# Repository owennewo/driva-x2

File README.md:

# driva-x2
Experimental dual BLDC board for use with [SimpleFOC](https://simplefoc.com)

This board will cost about $200 for 5 units from JLCPCB. Include are [gerber zip](https://github.com/owennewo/driva-x2/blob/main/kicad/gerber/driva-x2.zip), [BOM](https://github.com/owennewo/driva-x2/blob/main/kicad/assembly/driva-x2-bom.csv) and [POS](https://github.com/owennewo/driva-x2/blob/main/kicad/assembly/driva-x2-all-pos.csv).  Designed in Kicad.  This is pre-alpha quality e.g. I'm uncertain how much of it will work.  I've tested v0.5 with motor and hall sensors on left motor and that worked.

 - dual motor drivers using 3x btn8982 or ixf0007s
 - each motor has hall and spi port (untested)
 - prog (swd, swdio), can (untested), usart and i2c (untested) ports
 - ubg-otg (utested and without 5v attached)
 - onboard mpu6050 for 6 axis imu

Note JLCPCB won't do through hole components therefore all power, motor, comms ports will need to be hand solder as will the 1000uF cap.  

The BOM and Pick/Place/POS file are here:
https://github.com/owennewo/driva-x2/tree/main/kicad/assembly 

[PDF Schematic](./kicad/docs/driva-x2.pdf)

The gerber files are here:
https://github.com/owennewo/driva-x2/tree/main/kicad/gerber

The BOM and Pick/Place/POS file are here:
https://github.com/owennewo/driva-x2/tree/main/kicad/assembly

 * v0.5 - First attempt (partly working - problems with mpu6050, can and LDO)
 * v0.9 - Second attempt (fixed above hopefully - awaiting order from JLCPCB)

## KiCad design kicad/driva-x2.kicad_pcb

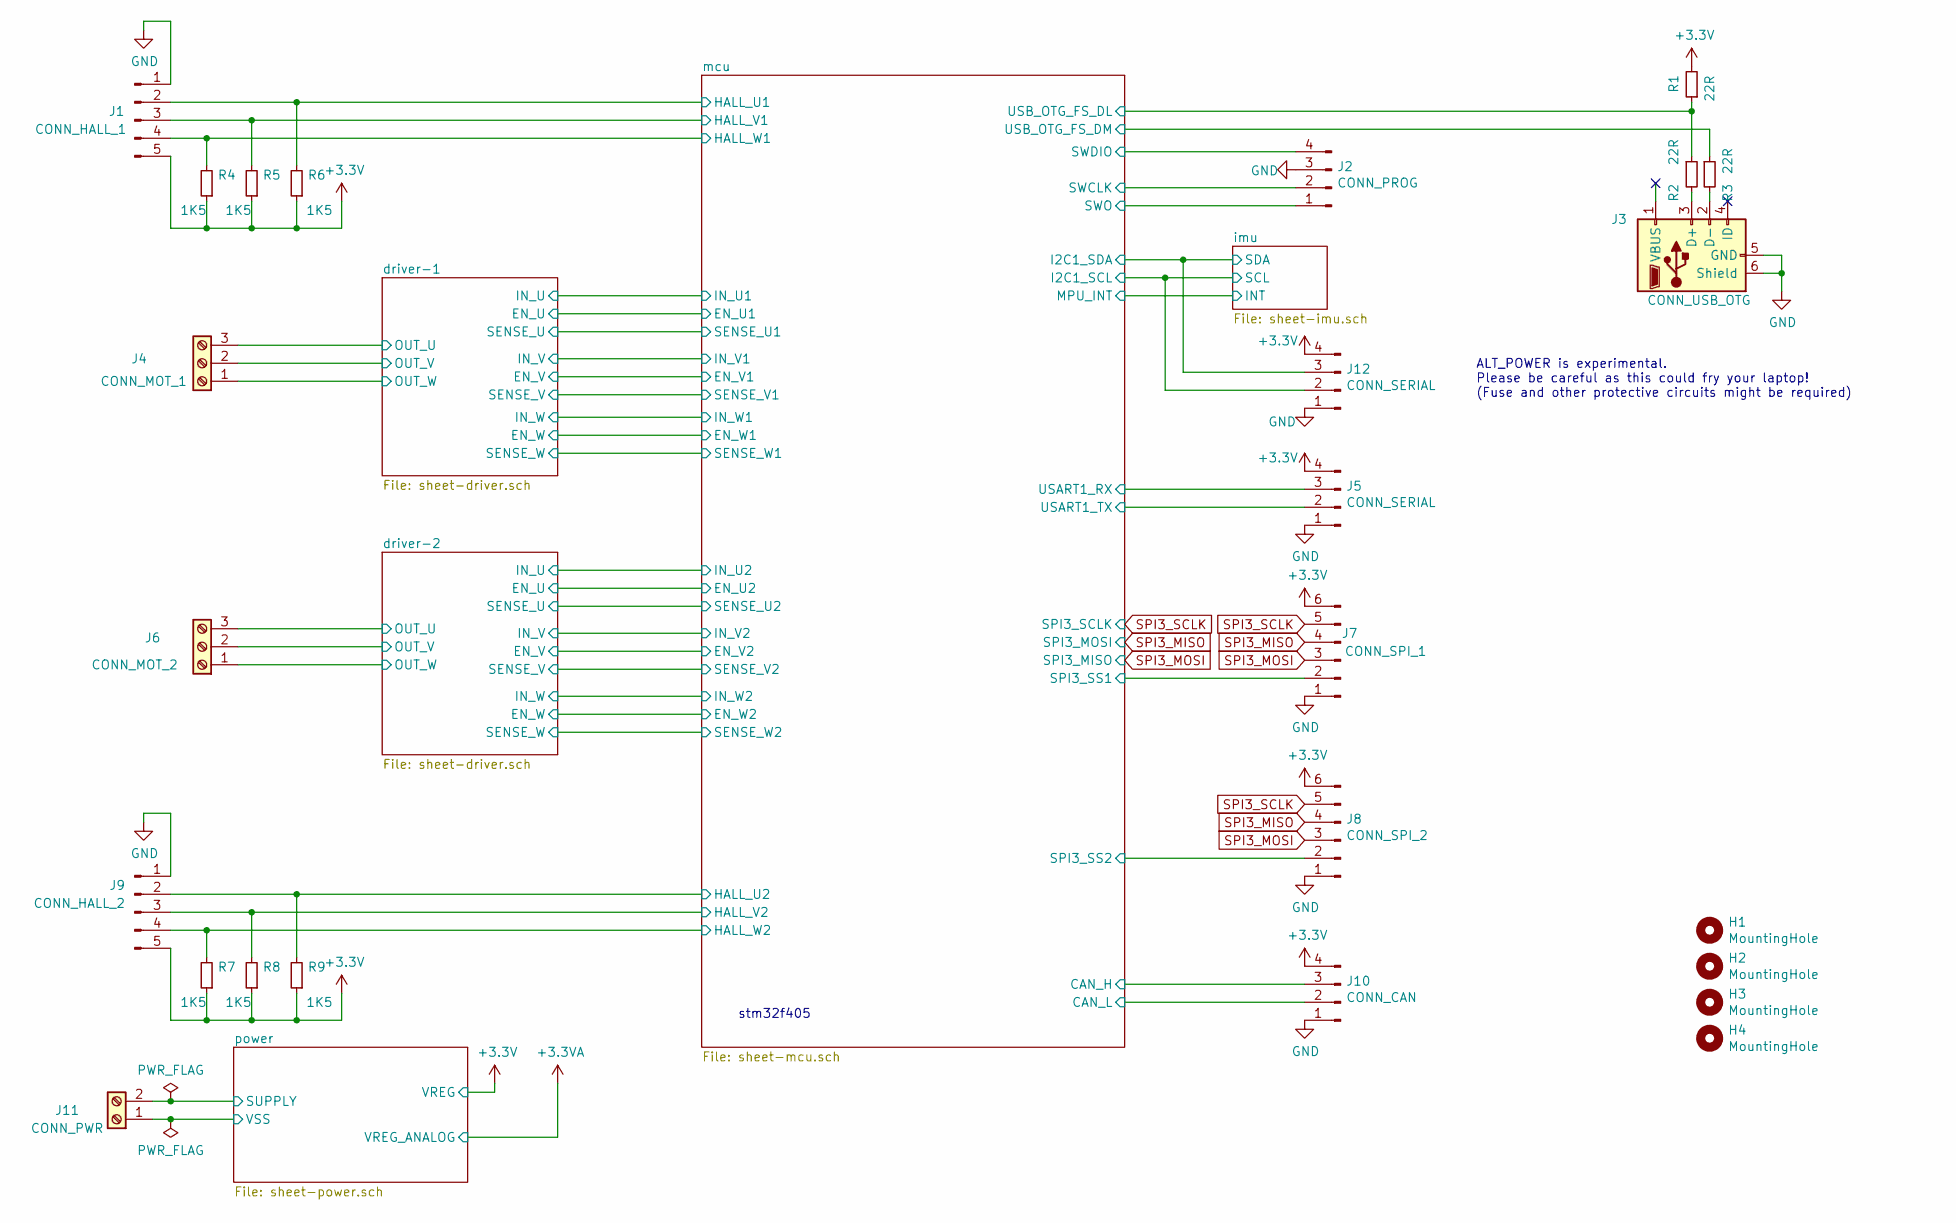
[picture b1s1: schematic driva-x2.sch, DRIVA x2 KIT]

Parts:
H1, H2, H3, H4: MountingHole; MountingHole_3.2mm_M3_ISO14580_Pad_TopBottom
J1: CONN_HALL_1; PinHeader_1x05_P2.54mm_Vertical
J2: CONN_PROG; PinHeader_1x04_P2.54mm_Vertical
J3: CONN_USB_OTG; USB_Micro-B_Wuerth_629105150521
J4: CONN_MOT_1; TerminalBlock_Altech_AK300-3_P5.00mm
J5, J12: CONN_SERIAL; PinHeader_1x04_P2.54mm_Vertical
J6: CONN_MOT_2; TerminalBlock_Altech_AK300-3_P5.00mm
J7: CONN_SPI_1; PinHeader_1x06_P2.54mm_Vertical
J8: CONN_SPI_2; PinHeader_1x06_P2.54mm_Vertical
J9: CONN_HALL_2; PinHeader_1x05_P2.54mm_Vertical
J10: CONN_CAN; PinHeader_1x04_P2.54mm_Vertical
J11: CONN_PWR; TerminalBlock_Altech_AK300-2_P5.00mm
R1, R2, R3: 22R; R_0402_1005Metric
R4, R5, R6, R7, R8, R9: 1K5; R_0402_1005Metric

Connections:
+3V3: J1.5, J5.4, J7.6, J8.6, J9.5, J10.4, J12.4, R1.2, R4.1, R5.1, R6.1, R7.1, R8.1, R9.1; also elsewhere on the board
/driver-1/OUT_U: J4.3; also elsewhere on the board
/driver-1/OUT_V: J4.2; also elsewhere on the board
/driver-1/OUT_W: J4.1; also elsewhere on the board
/driver-2/OUT_U: J6.3; also elsewhere on the board
/driver-2/OUT_V: J6.2; also elsewhere on the board
/driver-2/OUT_W: J6.1; also elsewhere on the board
/mcu/CAN_H: J10.3; also elsewhere on the board
/mcu/CAN_L: J10.2; also elsewhere on the board
/mcu/HALL_U1: J1.2, R6.2; also elsewhere on the board
/mcu/HALL_U2: J9.2, R9.2; also elsewhere on the board
/mcu/HALL_V1: J1.3, R5.2; also elsewhere on the board
/mcu/HALL_V2: J9.3, R8.2; also elsewhere on the board
/mcu/HALL_W1: J1.4, R4.2; also elsewhere on the board
/mcu/HALL_W2: J9.4, R7.2; also elsewhere on the board
/mcu/I2C1_SCL: J12.2; also elsewhere on the board
/mcu/I2C1_SDA: J12.3; also elsewhere on the board
/mcu/SPI3_SS1: J7.2; also elsewhere on the board
/mcu/SPI3_SS2: J8.2; also elsewhere on the board
/mcu/SWCLK: J2.2; also elsewhere on the board
/mcu/SWDIO: J2.4; also elsewhere on the board
/mcu/SWO: J2.1; also elsewhere on the board
/mcu/USART1_RX: J5.3; also elsewhere on the board
/mcu/USART1_TX: J5.2; also elsewhere on the board
/mcu/USB_OTG_FS_DL: R1.1, R2.1; also elsewhere on the board
/mcu/USB_OTG_FS_DM: R3.1; also elsewhere on the board
GND: J1.1, J2.3, J3.5 (GND), J3.6 (Shield), J5.1, J7.1, J8.1, J9.1, J10.1, J11.1, J12.1; also elsewhere on the board
unnamed: J3.2 (D-), R3.2
unnamed: J3.3 (D+), R2.2
SPI3_MISO: J7.4, J8.4; also elsewhere on the board
SPI3_MOSI: J7.3, J8.3; also elsewhere on the board
SPI3_SCLK: J7.5, J8.5; also elsewhere on the board
VCC: J11.2; also elsewhere on the board

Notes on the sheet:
stm32f405
ALT_POWER is experimental. Please be careful as this could fry your laptop! (Fuse and other protective circuits might be required)

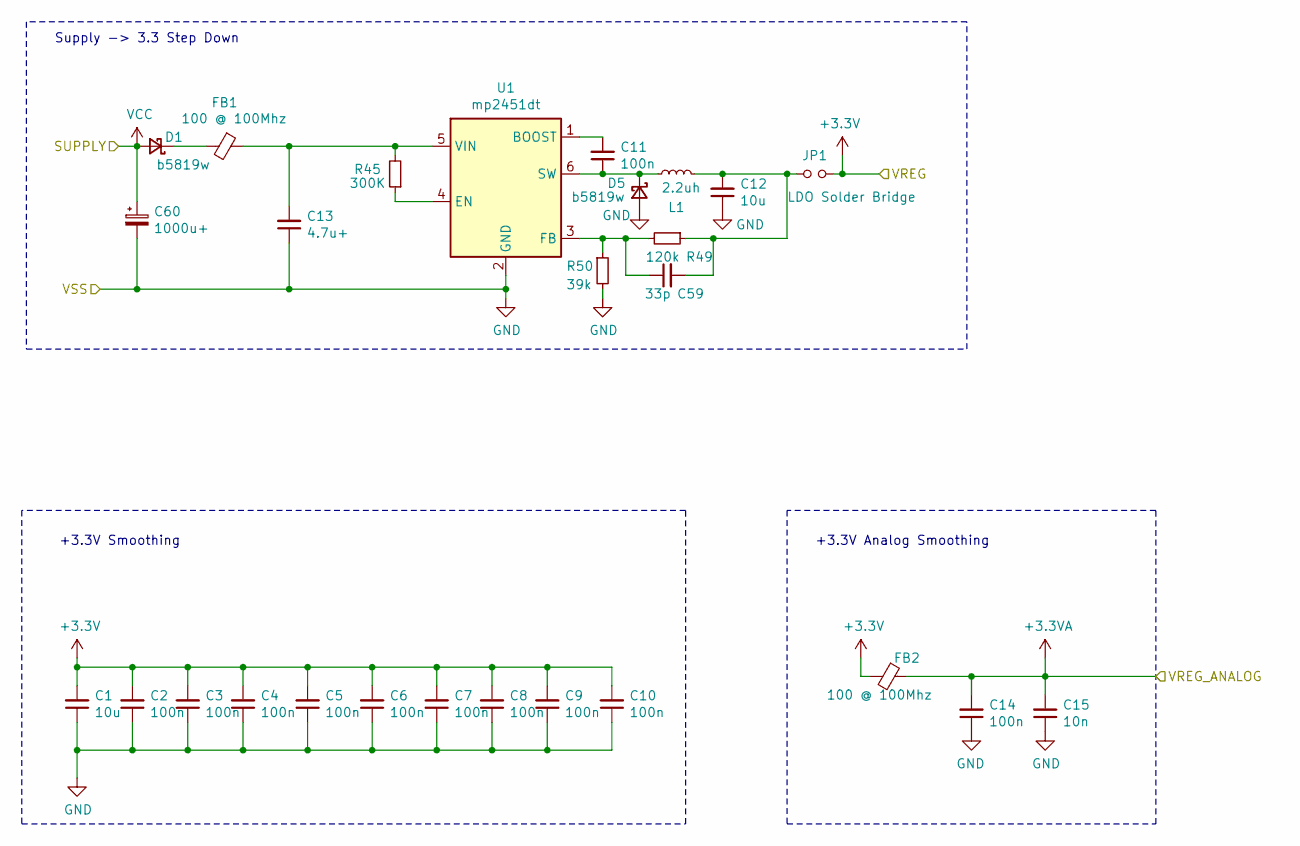
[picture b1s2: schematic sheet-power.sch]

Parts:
C1: 10u; C_0603_1608Metric
C2, C3, C4, C5, C6, C7, C8, C9, C10, C11, C14: 100n; C_0402_1005Metric
C12: 10u; C_0402_1005Metric
C13: 4.7u+; C_0805_2012Metric
C15: 10n; C_0402_1005Metric
C59: 33p; C_0402_1005Metric
C60: 1000u+; CP_Radial_D8.0mm_P5.00mm
D1, D5: b5819w; D_SOD-123
FB1, FB2: 100 @ 100Mhz; L_0805_2012Metric
JP1: LDO Solder Bridge; SolderJumper-2_P1.3mm_Bridged_Pad1.0x1.5mm
L1: 2.2uh; L_1210_3225Metric
R45: 300K; R_0402_1005Metric
R49: 120k; R_0402_1005Metric
R50: 39k; R_0402_1005Metric
U1: mp2451dt; SOT-23-6

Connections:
+3.3VA: C14.2, C15.2, FB2.1; also elsewhere on the board
+3V3: C1.2, C2.2, C3.2, C4.2, C5.2, C6.2, C7.2, C8.2, C9.2, C10.2, FB2.2, JP1.2; also elsewhere on the board
GND: C1.1, C2.1, C3.1, C4.1, C5.1, C6.1, C7.1, C8.1, C9.1, C10.1, C12.1, C13.1, C14.1, C15.1, C60.2, D5.2 (A), R50.2, U1.2 (GND); also elsewhere on the board
unnamed: C11.1, D5.1 (K), L1.1, U1.6 (SW)
unnamed: C11.2, U1.1 (BOOST)
unnamed: C12.2, C59.2, JP1.1, L1.2, R49.1
unnamed: C13.2, FB1.1, R45.2, U1.5 (VIN)
unnamed: C59.1, R49.2, R50.1, U1.3 (FB)
unnamed: D1.1 (K), FB1.2
unnamed: R45.1, U1.4 (EN)
VCC: C60.1, D1.2 (A); also elsewhere on the board

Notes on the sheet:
+3.3V Smoothing
+3.3V Analog Smoothing
Supply -> 3.3 Step Down

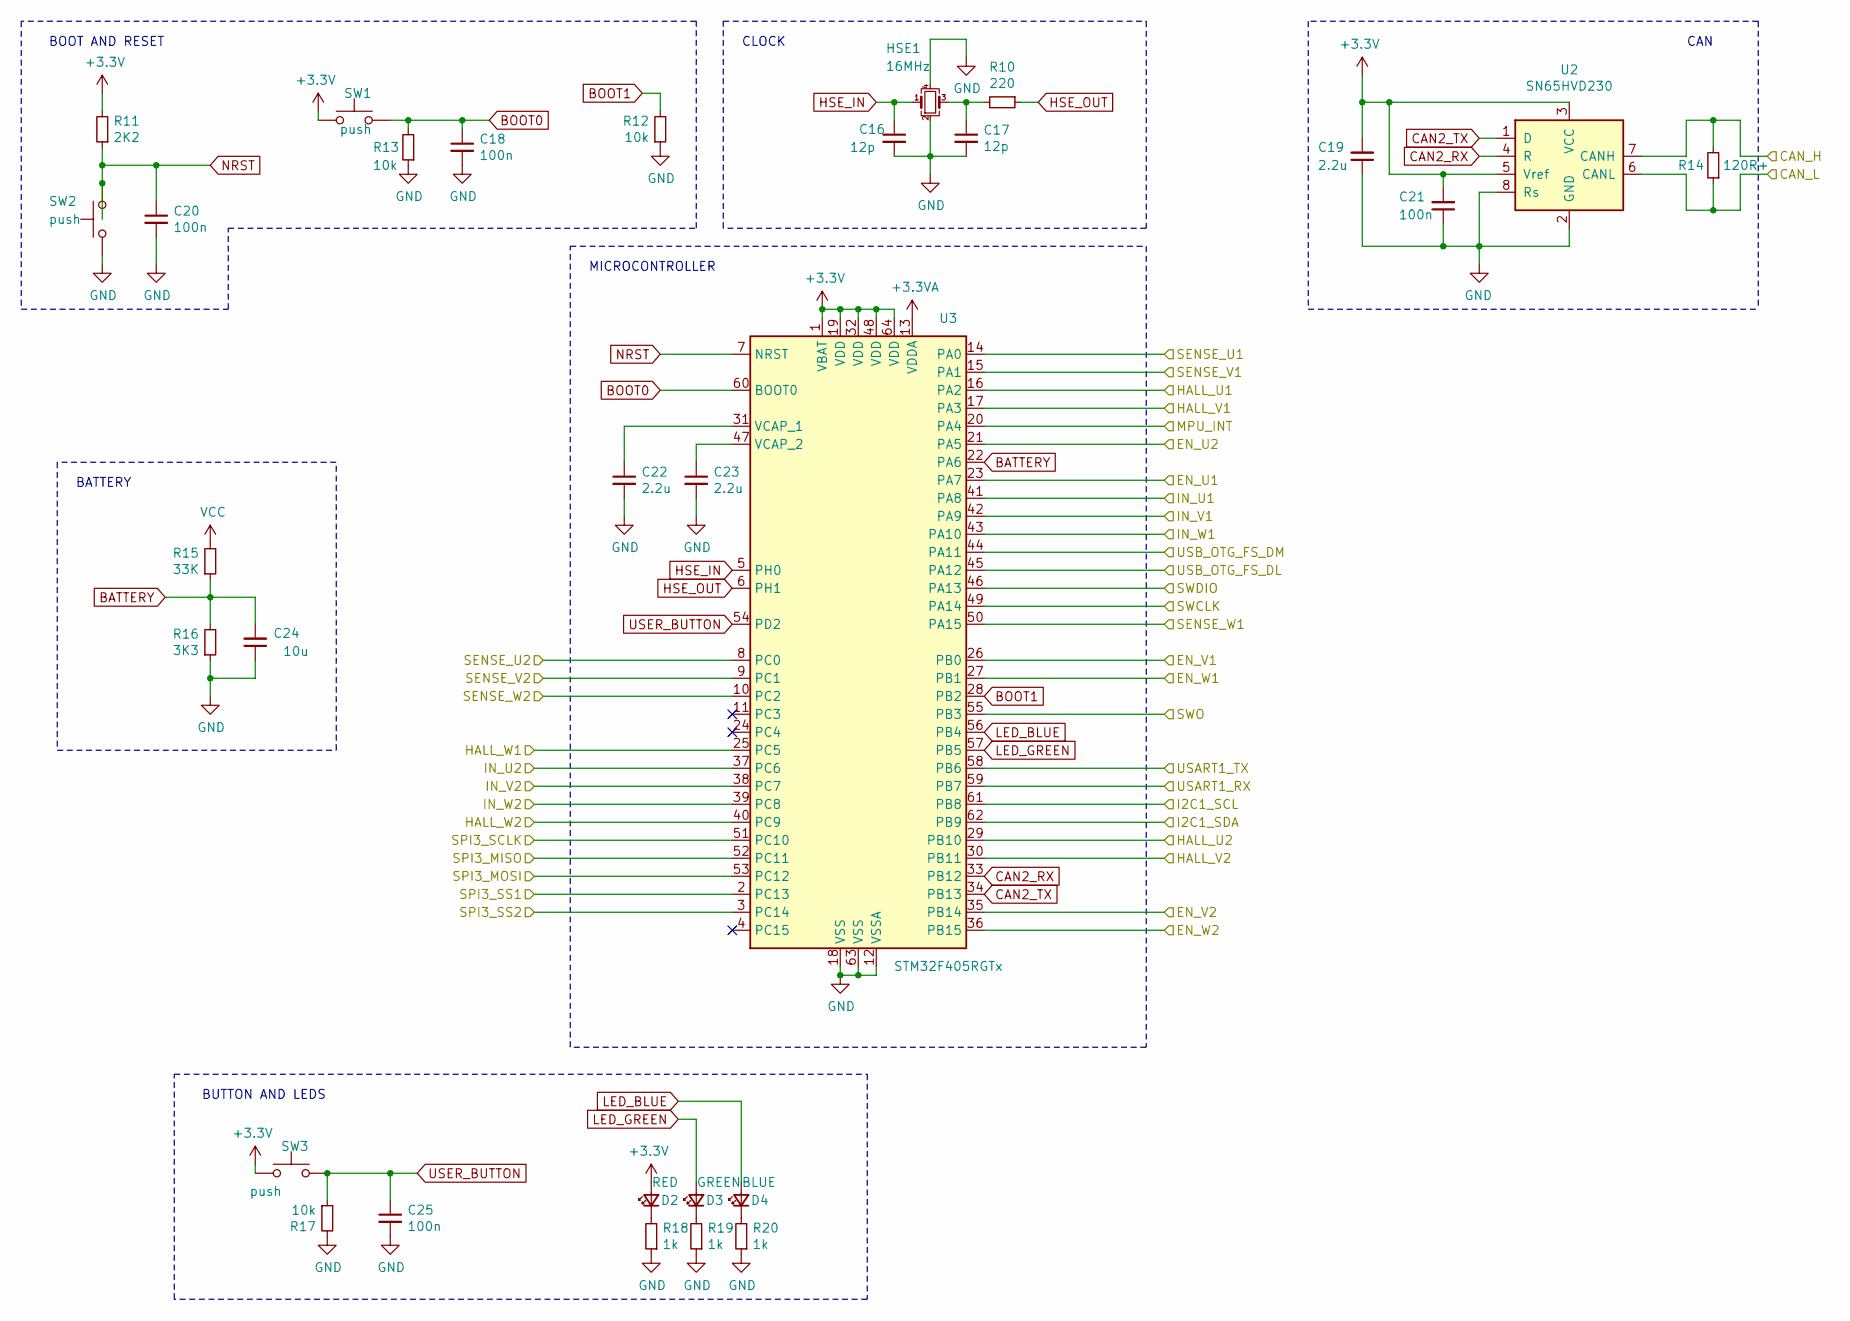
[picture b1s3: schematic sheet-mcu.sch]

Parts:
C16, C17: 12p; C_0402_1005Metric
C18, C20, C21, C25: 100n; C_0402_1005Metric
C19, C22, C23: 2.2u; C_0603_1608Metric
C24: 10u; C_0603_1608Metric
D2: RED; LED_0603_1608Metric
D3: GREEN; LED_0603_1608Metric
D4: BLUE; LED_0603_1608Metric
HSE1: 16MHz; Crystal_SMD_3225-4Pin_3.2x2.5mm
R10: 220; R_0402_1005Metric
R11: 2K2; R_0603_1608Metric
R12, R13, R17: 10k; R_0402_1005Metric
R14: 120R+; R_1206_3216Metric
R15: 33K; R_0402_1005Metric
R16: 3K3; R_0402_1005Metric
R18, R19, R20: 1k; R_0402_1005Metric
SW1, SW2, SW3: push; SW_Push_SPST_NO_Alps_SKRK
U2: SN65HVD230; SOIC-8_3.9x4.9mm_P1.27mm
U3: STM32F405RGTx; LQFP-64_10x10mm_P0.5mm

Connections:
+3.3VA: U3.13 (VDDA); also elsewhere on the board
+3V3: C19.2, C21.2, D2.2 (A), R11.2, SW1.1, SW3.1, U2.3 (VCC), U2.5 (Vref), U3.1 (VBAT), U3.19 (VDD), U3.32 (VDD), U3.48 (VDD), U3.64 (VDD); also elsewhere on the board
/driver-1/EN_U: U3.23 (PA7); also elsewhere on the board
/driver-1/EN_V: U3.26 (PB0); also elsewhere on the board
/driver-1/EN_W: U3.27 (PB1); also elsewhere on the board
/driver-1/IN_U: U3.41 (PA8); also elsewhere on the board
/driver-1/IN_V: U3.42 (PA9); also elsewhere on the board
/driver-1/IN_W: U3.43 (PA10); also elsewhere on the board
/driver-1/SENSE_U: U3.14 (PA0); also elsewhere on the board
/driver-1/SENSE_V: U3.15 (PA1); also elsewhere on the board
/driver-1/SENSE_W: U3.50 (PA15); also elsewhere on the board
/driver-2/EN_U: U3.21 (PA5); also elsewhere on the board
/driver-2/EN_V: U3.35 (PB14); also elsewhere on the board
/driver-2/EN_W: U3.36 (PB15); also elsewhere on the board
/driver-2/IN_U: U3.37 (PC6); also elsewhere on the board
/driver-2/IN_V: U3.38 (PC7); also elsewhere on the board
/driver-2/IN_W: U3.39 (PC8); also elsewhere on the board
/driver-2/SENSE_U: U3.8 (PC0); also elsewhere on the board
/driver-2/SENSE_V: U3.9 (PC1); also elsewhere on the board
/driver-2/SENSE_W: U3.10 (PC2); also elsewhere on the board
/imu/INT: U3.20 (PA4); also elsewhere on the board
/mcu/CAN_H: R14.2, U2.7 (CANH); also elsewhere on the board
/mcu/CAN_L: R14.1, U2.6 (CANL); also elsewhere on the board
/mcu/HALL_U1: U3.16 (PA2); also elsewhere on the board
/mcu/HALL_U2: U3.29 (PB10); also elsewhere on the board
/mcu/HALL_V1: U3.17 (PA3); also elsewhere on the board
/mcu/HALL_V2: U3.30 (PB11); also elsewhere on the board
/mcu/HALL_W1: U3.25 (PC5); also elsewhere on the board
/mcu/HALL_W2: U3.40 (PC9); also elsewhere on the board
/mcu/I2C1_SCL: U3.61 (PB8); also elsewhere on the board
/mcu/I2C1_SDA: U3.62 (PB9); also elsewhere on the board
/mcu/SPI3_SS1: U3.2 (PC13); also elsewhere on the board
/mcu/SPI3_SS2: U3.3 (PC14); also elsewhere on the board
/mcu/SWCLK: U3.49 (PA14); also elsewhere on the board
/mcu/SWDIO: U3.46 (PA13); also elsewhere on the board
/mcu/SWO: U3.55 (PB3); also elsewhere on the board
/mcu/USART1_RX: U3.59 (PB7); also elsewhere on the board
/mcu/USART1_TX: U3.58 (PB6); also elsewhere on the board
/mcu/USB_OTG_FS_DL: U3.45 (PA12); also elsewhere on the board
/mcu/USB_OTG_FS_DM: U3.44 (PA11); also elsewhere on the board
BATTERY: C24.2, R15.1, R16.2, U3.22 (PA6)
BOOT0: C18.1, R13.2, SW1.2, U3.60 (BOOT0)
BOOT1: R12.2, U3.28 (PB2)
CAN2_RX: U2.4 (R), U3.33 (PB12)
CAN2_TX: U2.1 (D), U3.34 (PB13)
GND: C16.2, C17.2, C18.2, C19.1, C20.2, C21.1, C22.2, C23.2, C24.1, C25.2, HSE1.2, HSE1.4, R12.1, R13.1, R16.1, R17.2, R18.1, R19.1, R20.1, SW2.1, U2.2 (GND), U2.8 (Rs), U3.12 (VSSA), U3.18 (VSS), U3.63 (VSS); also elsewhere on the board
HSE_IN: C16.1, HSE1.1, U3.5 (PH0)
HSE_OUT: R10.1, U3.6 (PH1)
LED_BLUE: D4.2 (A), U3.56 (PB4)
LED_GREEN: D3.2 (A), U3.57 (PB5)
NRST: C20.1, R11.1, SW2.2, U3.7 (NRST)
unnamed: C17.1, HSE1.3, R10.2
unnamed: C22.1, U3.31 (VCAP_1)
unnamed: C23.1, U3.47 (VCAP_2)
unnamed: D2.1 (K), R18.2
unnamed: D3.1 (K), R19.2
unnamed: D4.1 (K), R20.2
SPI3_MISO: U3.53 (PC12); also elsewhere on the board
SPI3_MOSI: U3.52 (PC11); also elsewhere on the board
SPI3_SCLK: U3.51 (PC10); also elsewhere on the board
USER_BUTTON: C25.1, R17.1, SW3.2, U3.54 (PD2)
VCC: R15.2; also elsewhere on the board

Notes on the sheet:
MICROCONTROLLER
BOOT AND RESET
CLOCK
CAN
BATTERY
BUTTON AND LEDS

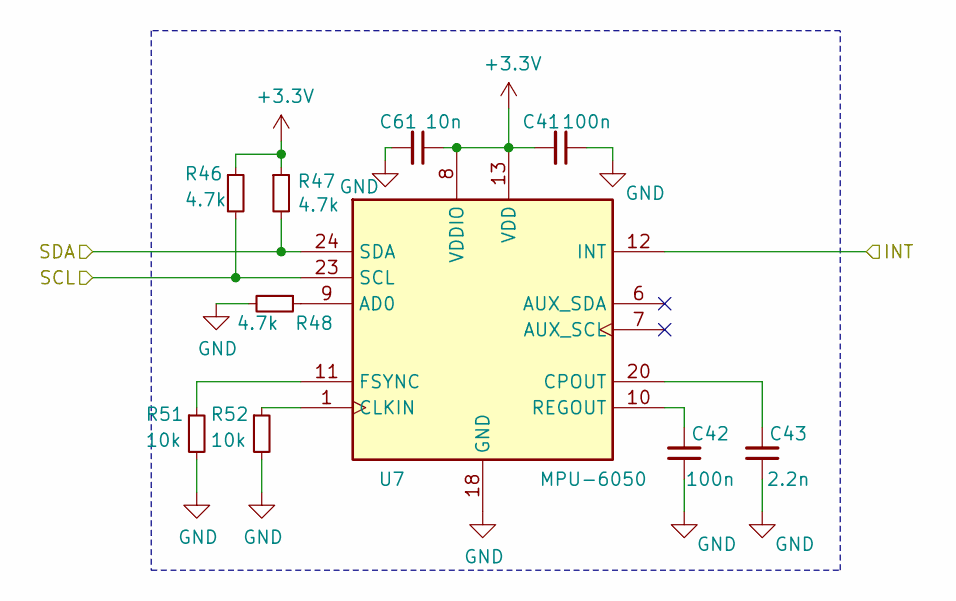
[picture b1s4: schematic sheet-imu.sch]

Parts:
C41, C42: 100n; C_0402_1005Metric
C43: 2.2n; C_0402_1005Metric
C61: 10n; C_0402_1005Metric
R46, R47, R48: 4.7k; R_0402_1005Metric
R51, R52: 10k; R_0402_1005Metric
U7: MPU-6050; InvenSense_QFN-24_4x4mm_P0.5mm

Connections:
+3V3: C41.2, C61.1, R46.1, R47.1, U7.8 (VDDIO), U7.13 (VDD); also elsewhere on the board
/imu/INT: U7.12 (INT); also elsewhere on the board
/mcu/I2C1_SCL: R46.2, U7.23 (SCL); also elsewhere on the board
/mcu/I2C1_SDA: R47.2, U7.24 (SDA); also elsewhere on the board
GND: C41.1, C42.1, C43.1, C61.2, R48.2, R51.2, R52.2, U7.18 (GND); also elsewhere on the board
unnamed: C42.2, U7.10 (REGOUT)
unnamed: C43.2, U7.20 (CPOUT)
unnamed: R48.1, U7.9 (AD0)
unnamed: R51.1, U7.11 (FSYNC)
unnamed: R52.1, U7.1 (CLKIN)

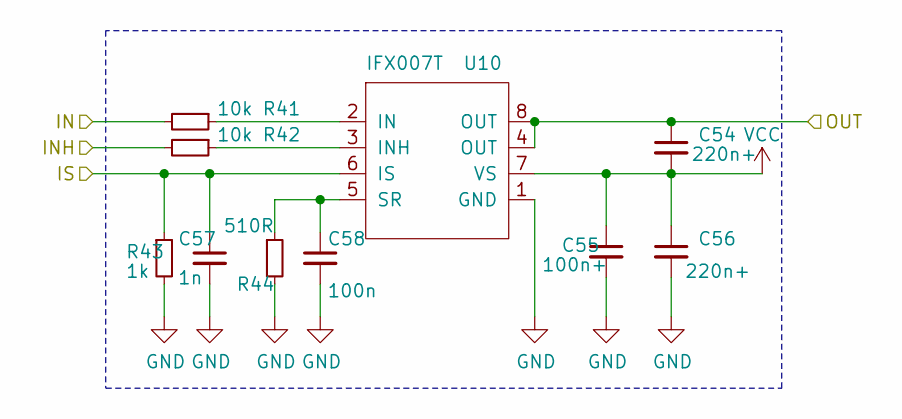
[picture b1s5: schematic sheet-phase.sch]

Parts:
C44, C46: 220n+; C_0603_1608Metric
C45: 100n+; C_0603_1608Metric
C47: 1n; C_0402_1005Metric
C48: 100n; C_0402_1005Metric
R33, R34: 10k; R_0402_1005Metric
R35: 1k; R_0402_1005Metric
R36: 510R; R_0402_1005Metric
U8: IFX007T; TO-263-7_TabPin8

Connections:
/driver-1/EN_U: R34.2; also elsewhere on the board
/driver-1/IN_U: R33.2; also elsewhere on the board
/driver-1/OUT_U: C44.1, U8.4 (OUT), U8.8 (OUT); also elsewhere on the board
/driver-1/SENSE_U: C47.1, R35.1, U8.6 (IS); also elsewhere on the board
GND: C45.2, C46.2, C47.2, C48.2, R35.2, R36.2, U8.1 (GND); also elsewhere on the board
unnamed: C48.1, R36.1, U8.5 (SR)
unnamed: R33.1, U8.2 (IN)
unnamed: R34.1, U8.3 (INH)
VCC: C44.2, C45.1, C46.1, U8.7 (VS); also elsewhere on the board

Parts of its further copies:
C26, C28, C31, C33, C36, C38, C49, C51, C54, C56: 220n+; C_0603_1608Metric
C27, C32, C37, C50, C55: 100n+; C_0603_1608Metric
C29, C34, C39, C52, C57: 1n; C_0402_1005Metric
C30, C35, C40, C53, C58: 100n; C_0402_1005Metric
R21, R22, R25, R26, R29, R30, R37, R38, R41, R42: 10k; R_0402_1005Metric
R23, R27, R31, R39, R43: 1k; R_0402_1005Metric
R24, R28, R32, R40, R44: 510R; R_0402_1005Metric
U4, U5, U6, U9, U10: IFX007T; TO-263-7_TabPin8

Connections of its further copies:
/driver-1/EN_V: R38.2; also elsewhere on the board
/driver-1/EN_W: R42.2; also elsewhere on the board
/driver-1/IN_V: R37.2; also elsewhere on the board
/driver-1/IN_W: R41.2; also elsewhere on the board
/driver-1/OUT_V: C49.1, U9.4 (OUT), U9.8 (OUT); also elsewhere on the board
/driver-1/OUT_W: C54.1, U10.4 (OUT), U10.8 (OUT); also elsewhere on the board
/driver-1/SENSE_V: C52.1, R39.1, U9.6 (IS); also elsewhere on the board
/driver-1/SENSE_W: C57.1, R43.1, U10.6 (IS); also elsewhere on the board
/driver-2/EN_U: R22.2; also elsewhere on the board
/driver-2/EN_V: R26.2; also elsewhere on the board
/driver-2/EN_W: R30.2; also elsewhere on the board
/driver-2/IN_U: R21.2; also elsewhere on the board
/driver-2/IN_V: R25.2; also elsewhere on the board
/driver-2/IN_W: R29.2; also elsewhere on the board
/driver-2/OUT_U: C26.1, U4.4 (OUT), U4.8 (OUT); also elsewhere on the board
/driver-2/OUT_V: C31.1, U5.4 (OUT), U5.8 (OUT); also elsewhere on the board
/driver-2/OUT_W: C36.1, U6.4 (OUT), U6.8 (OUT); also elsewhere on the board
/driver-2/SENSE_U: C29.1, R23.1, U4.6 (IS); also elsewhere on the board
/driver-2/SENSE_V: C34.1, R27.1, U5.6 (IS); also elsewhere on the board
/driver-2/SENSE_W: C39.1, R31.1, U6.6 (IS); also elsewhere on the board
GND: C27.2, C28.2, C29.2, C30.2, C32.2, C33.2, C34.2, C35.2, C37.2, C38.2, C39.2, C40.2, C50.2, C51.2, C52.2, C53.2, C55.2, C56.2, C57.2, C58.2, R23.2, R24.2, R27.2, R28.2, R31.2, R32.2, R39.2, R40.2, R43.2, R44.2, U4.1 (GND), U5.1 (GND), U6.1 (GND), U9.1 (GND), U10.1 (GND); also elsewhere on the board
unnamed: C30.1, R24.1, U4.5 (SR)
unnamed: C35.1, R28.1, U5.5 (SR)
unnamed: C40.1, R32.1, U6.5 (SR)
unnamed: C53.1, R40.1, U9.5 (SR)
unnamed: C58.1, R44.1, U10.5 (SR)
unnamed: R21.1, U4.2 (IN)
unnamed: R22.1, U4.3 (INH)
unnamed: R25.1, U5.2 (IN)
unnamed: R26.1, U5.3 (INH)
unnamed: R29.1, U6.2 (IN)
unnamed: R30.1, U6.3 (INH)
unnamed: R37.1, U9.2 (IN)
unnamed: R38.1, U9.3 (INH)
unnamed: R41.1, U10.2 (IN)
unnamed: R42.1, U10.3 (INH)
VCC: C26.2, C27.1, C28.1, C31.2, C32.1, C33.1, C36.2, C37.1, C38.1, C49.2, C50.1, C51.1, C54.2, C55.1, C56.1, U4.7 (VS), U5.7 (VS), U6.7 (VS), U9.7 (VS), U10.7 (VS); also elsewhere on the board

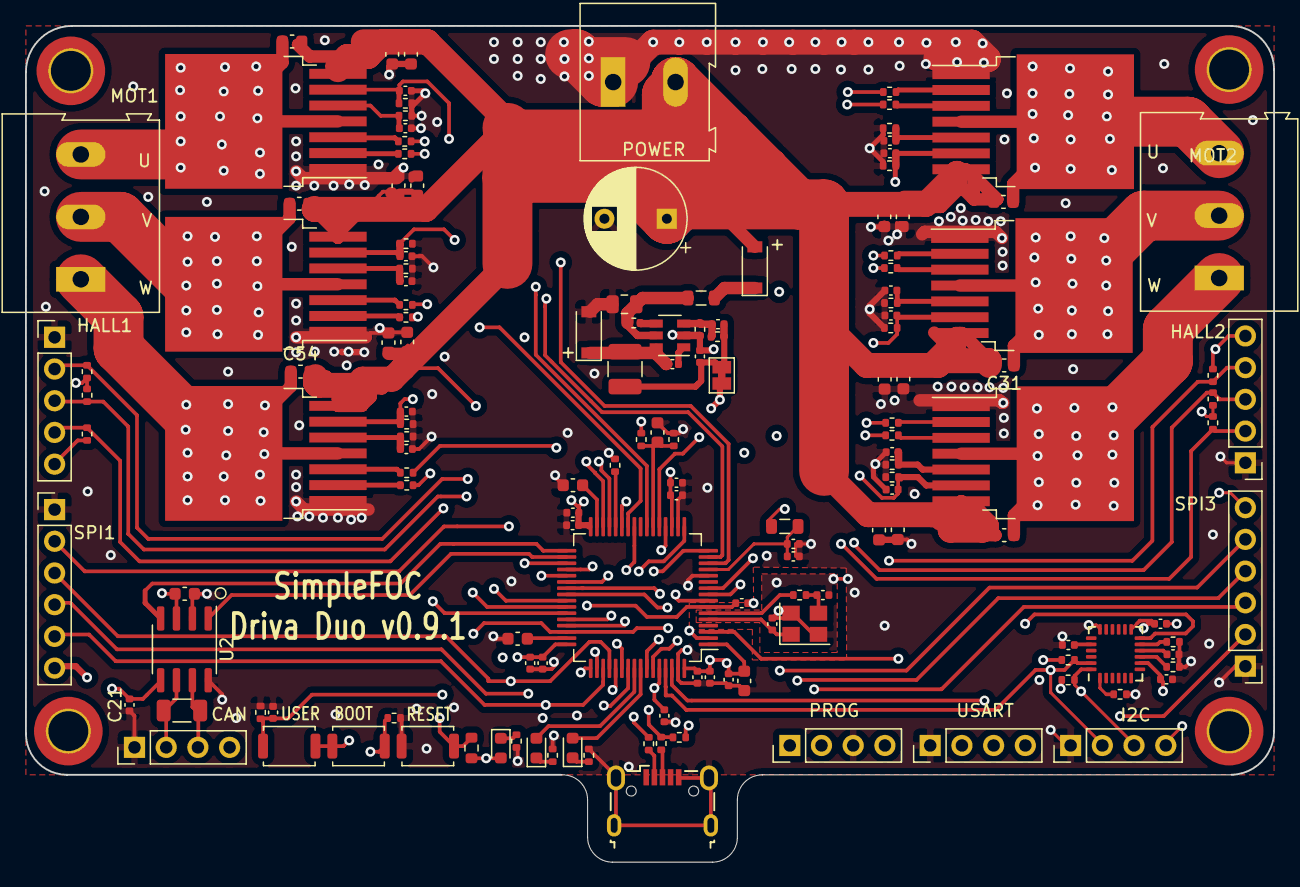
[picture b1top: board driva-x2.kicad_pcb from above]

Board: 4 copper layers, 100.0 x 67.0 mm, 152 parts (0 on the bottom side), 100 nets.

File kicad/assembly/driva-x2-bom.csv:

Id,Designator,Footprint,Quantity,Designation,LCSC Part Number
2,"C56,C54,C51,C49,C46,C44,C38,C36,C33,C31,C28,C26",0603,12,220n+,C21120
3,"C55,C50,C45,C37,C32,C27",0603,6,100n+,C14663
4,"R52,R51,R12,R13,R17,R21,R22,R25,R26,R29,R30,R33,R34,R37,R38,R41,R42",0402,17,10k,C25744
5,R14,1206,1,120R+,C22107
7,R11,0603,1,2K2,C4190
10,"C11,C2,C3,C4,C5,C6,C7,C8,C9,C10,C14,C18,C20,C25,C30,C35,C40,C41,C42,C48,C53,C58,C21",0402,23,100n,C1525
11,C59,0402,1,33p,C1562
12,C12,0402,1,10u,C15525
13,U1,SOT-23-6L,1,mp2451dt,C14123
14,R50,0402,1,39k,C25783
15,R49,0402,1,120k,C25750
16,"R48,R47,R46",0402,3,4.7k,C25900
17,R45,0402,1,300K,C25774
18,L1,1210,1,2.2uh,C86074
21,"D5,D1",SOD-123,2,b5819w,C8598
22,"C61,C15",0402,2,10n,C15195
23,C13,0805,1,4.7u+,C1779
24,"C1,C24",0603,2,10u,C19702
25,"C16,C17",0402,2,12p,C1547
26,"C19,C22,C23",0603,3,2.2u,C23630
27,"C29,C34,C39,C47,C52,C57",0402,6,1n,C1523
28,C43,0402,1,2.2n,C1531
29,D2,LED_0603,1,RED,C2286
30,D3,LED_0603,1,GREEN,C72043
31,D4,LED_0603,1,BLUE,C72041
32,"FB1,FB2",0805,2,100 @ 100Mhz,C1015
33,HSE1,SMD-CRY-3225_4P,1,16MHz,C13738
42,"R1,R2,R3",0402,3,22R,C25092
43,"R4,R5,R6,R7,R8,R9",0402,6,1K5,C25867
44,R10,0402,1,220,C25091
45,R15,0402,1,33K,C25779
46,R16,0402,1,3K3,C25890
48,"R18,R19,R20,R23,R27,R31,R35,R39,R43",0402,9,1k,C11702
49,"R24,R28,R32,R36,R40,R44",0402,6,510R,C25123
50,"SW1,SW2,SW3",SW-SMD-2_3.0x4.0x1.7,3,push,C561519
51,U2,SOIC-8_3.9x4.9x1.27P,1,SN65HVD230,C12084
52,U3,LQFP-64_10.0x10.0x0.5P,1,STM32F405RGTx,C15742
53,"U4,U5,U6,U8,U9,U10",TO-263-7L,6,IFX007T,C74175
54,U7,QFN-24_EP_4.0x4.0x0.5P,1,MPU-6050,C24112

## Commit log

2020-11-30 adding v0.1 of driva x3 kit
2020-12-06 layout and bom complete - waiting on parts from jlcpcb
2021-02-05 Adding 0.9 version
2021-02-05 deleting old artefacts
2021-02-07 adding solder bridge and more vias under driver
2021-02-08 updating bom and pos files
2021-02-08 adding top layer
2021-02-13 v0.9.1 swapping can to 3.3v SN65HVD230
2021-02-13 updating pdf
